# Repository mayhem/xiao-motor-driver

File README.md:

# xiao-motor-driver
Hardware designs for the motor driver that works with Xiao boards

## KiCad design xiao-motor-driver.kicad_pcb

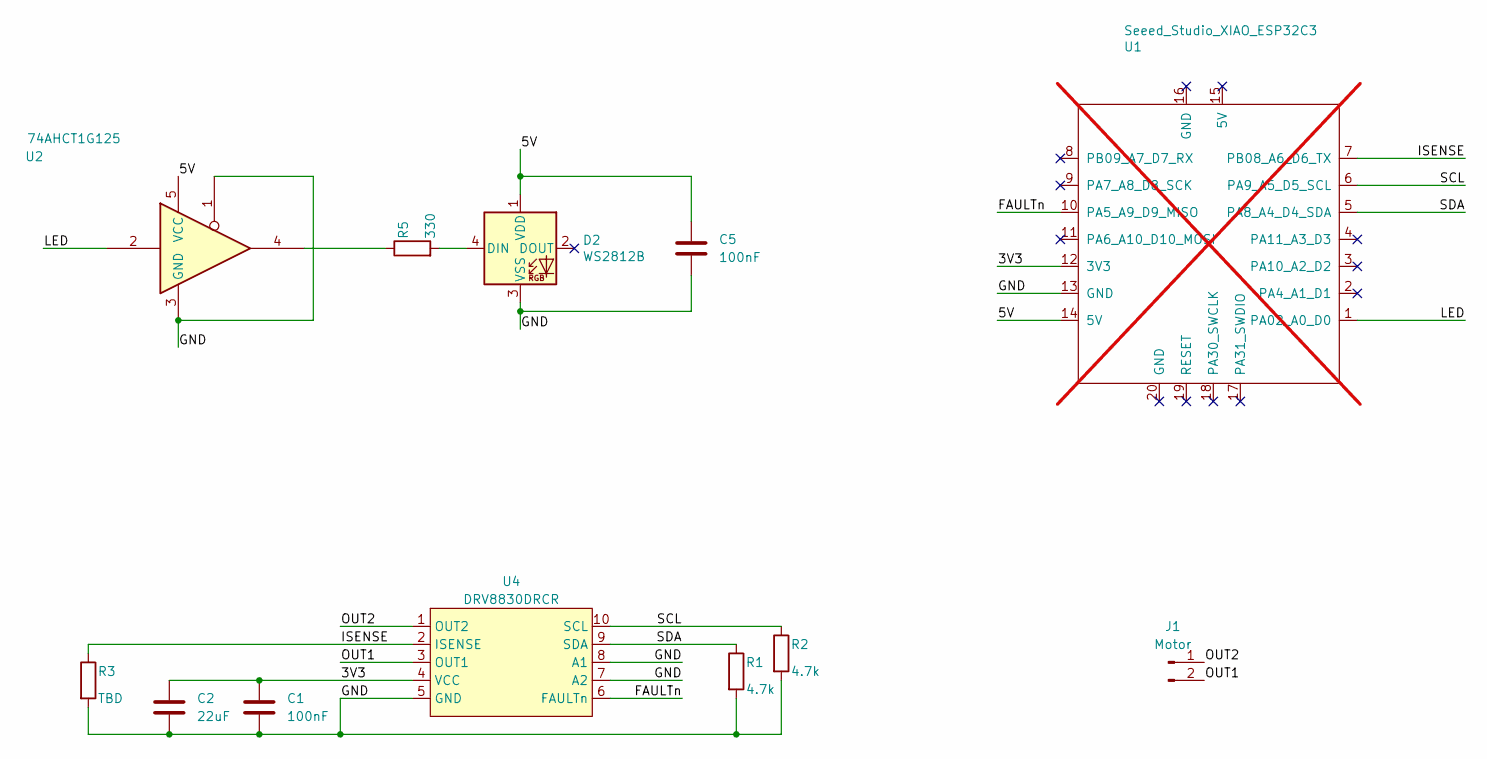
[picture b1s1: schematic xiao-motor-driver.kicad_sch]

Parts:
C1, C5: 100nF; C_0805_2012Metric
C2: 22uF; C_0805_2012Metric
D2: WS2812B; LED_WS2812B_PLCC4_5.0x5.0mm_P3.2mm
J1: Motor; PinHeader_1x02_P2.54mm_Vertical
R1, R2: 4.7k; R_0805_2012Metric
R3: TBD; R_0805_2012Metric
R5: 330; R_0805_2012Metric
U1: Seeed_Studio_XIAO_ESP32C3; XIAO-ESP32C3-14P-2.54-21X17.8MM; not fitted
U2: 74AHCT1G125; SOT-353_SC-70-5
U4: DRV8830DRCR; VSON-10-1EP_3x3mm_P0.5mm_EP1.65x2.4mm_ThermalVias

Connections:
/3V3: C1.1, C2.1, U1.12 (3V3), U4.4 (VCC)
/5V: C5.1, D2.1 (VDD), U1.14 (5V), U2.5 (VCC)
/FAULTn: U1.10 (PA5_A9_D9_MISO), U4.6 (FAULTn)
/GND: C1.2, C2.2, C5.2, D2.3 (VSS), R1.2, R2.2, R3.2, U1.13 (GND), U2.1, U2.3 (GND), U4.5 (GND), U4.7 (A2), U4.8 (A1), U4.11
/ISENSE: R3.1, U1.7 (PB08_A6_D6_TX), U4.2 (ISENSE)
/LED: U1.1 (PA02_A0_D0), U2.2
/OUT1: J1.2, U4.3 (OUT1)
/OUT2: J1.1, U4.1 (OUT2)
/SCL: R2.1, U1.6 (PA9_A5_D5_SCL), U4.10 (SCL)
/SDA: R1.1, U1.5 (PA8_A4_D4_SDA), U4.9 (SDA)
unnamed: D2.4 (DIN), R5.2
unnamed: R5.1, U2.4

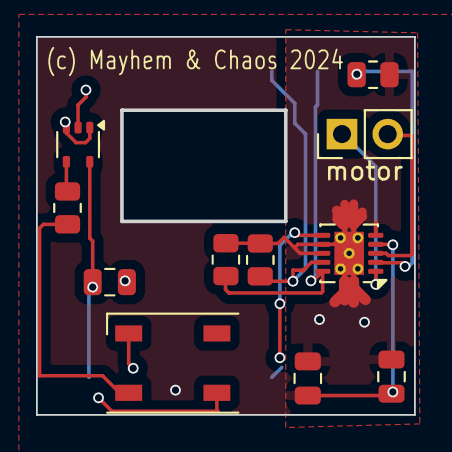
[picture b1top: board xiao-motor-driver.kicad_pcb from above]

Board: 2 copper layers, 20.9 x 20.9 mm, 12 parts (1 on the bottom side), 12 nets.

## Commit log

2024-05-22 First check in -- waiting for boards to arrive
